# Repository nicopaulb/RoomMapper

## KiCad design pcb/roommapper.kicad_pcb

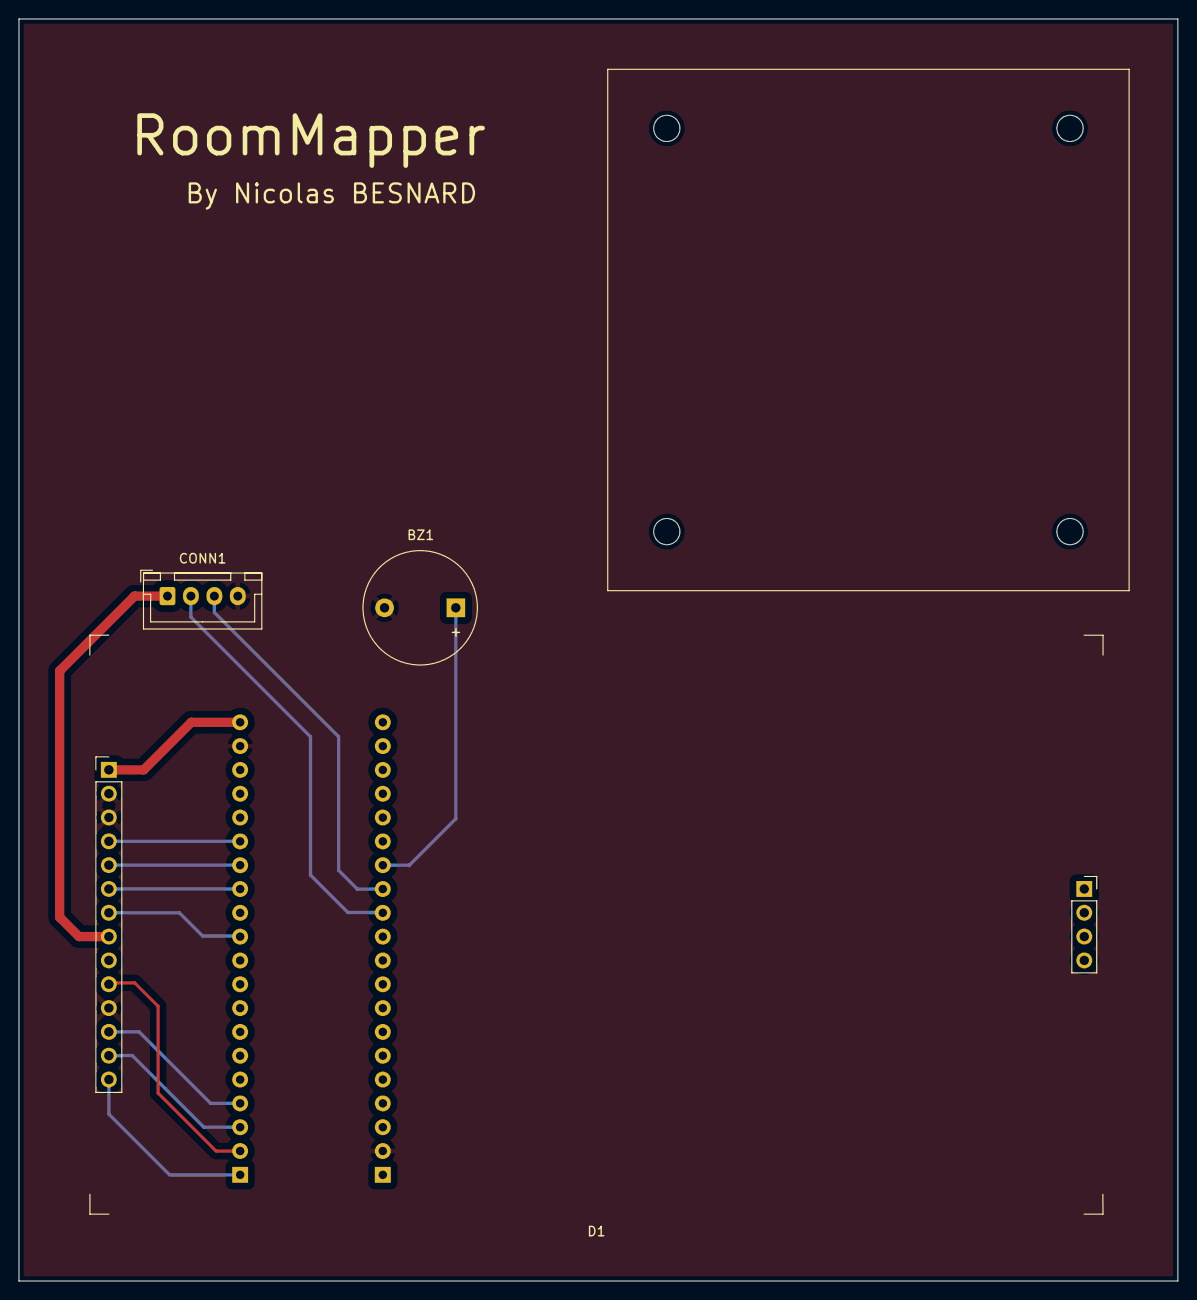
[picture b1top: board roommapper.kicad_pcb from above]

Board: 2 copper layers, 123.6 x 134.6 mm, 4 parts (1 on the bottom side), 14 nets.

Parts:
BZ1: Buzzer; Buzzer_12x9.5RM7.6
CONN1: RPLIDAR_C1; JST_XH_B4B-XH-A_1x04_P2.50mm_Vertical
D1: TFT_480x320; TFT_ILI9488_480x320
U2: STM32F411CEUx_BlackPill; STM32F4x1CxU6 WeActStudio

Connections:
3.3V: D1.1 (VCC), U2.20 (3.3V)
5V: CONN1.1 (VCC), D1.8 (LED), U2.18 (5V)
BUZZER: BZ1.1 (+), U2.27 (TIM2_CH2)
GND: BZ1.2 (-), CONN1.4 (GND), D1.2 (GND), D1.3 (CS), D1.11 (T_CS), U2.19 (GND)
ILI94488_CLK: D1.7 (SCK), U2.11 (SPI1_SCK)
ILI94488_DC: D1.5 (DC), U2.14 (PB6)
ILI94488_MOSI: D1.6 (SDI), U2.13 (SPI1_MOSI)
ILI94488_RST: D1.4 (RST), U2.15 (PB7)
RPLIDAR_RX: CONN1.2 (TX), U2.29 (USART2_RX)
RPLIDAR_TX: CONN1.3 (RX), U2.28 (USART2_TX)
XPT2046_CLK: D1.10 (T_CLK), U2.2 (SPI2_SCK)
XPT2046_INT: D1.14 (T_IRQ), U2.1 (PB12)
XPT2046_MISO: D1.13 (T_DO), U2.3 (SPI2_MISO)
XPT2046_MOSI: D1.12 (T_DIN), U2.4 (SPI2_MOSI)

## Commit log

2025-11-17 Init
2025-11-18 rplidar: implement parser for received messages from RPLidar devices
2025-11-18 test: implement template
2025-11-18 rplidar: fix label can only be part of a statement error
2025-11-18 test: fix test main signature
2025-11-19 rplidar: fix various bug
2025-11-19 test: add new unit tests
2025-11-20 rplidar: implement scan express request
2025-11-20 test: add test for scan express
2025-11-20 test: add new unit test
2025-11-20 rplidar: do not expect more multiple response when a new request is sent
2025-11-21 cubemx: configure project to match STM32 black pill dev board
2025-11-21 cubemx: update ioc file
2025-11-21 project: migrate to STM32CubeIDE 2.0.0
2025-11-26 global: update
2025-11-26 rplidar: add reset function
2025-11-27 rplidar: add blocking options for all requests
2025-11-27 test: fix unit test
2025-11-27 rplidar: add blocking mode for scan requests
2025-11-27 doc: add doxygen documentation for rplidar
2025-11-28 global: save workspace
2025-12-05 display: fix interrupt being triggered while communication is ongoing
2025-12-05 rplidar: fix unsync happening when multiple requests were sent at the same time
2025-12-05 map: add several new features
2025-12-05 rplidar: reduce reset delay from 1000ms to 600ms
2025-12-05 format
2025-12-05 project: update files
2025-12-07 test: fix unit tests
2025-12-08 rplidar: check health status at init
2025-12-08 format: implement formatting rules for code
2025-12-08 rplidar: update doc
2025-12-08 display: rename static functions
2025-12-08 menu: implement menu management and diag screen
2025-12-09 pcb: update
2025-12-10 diag: add exit button
2025-12-10 rplidar: add doc about measurement scaling factor
2025-12-10 buzzer: implement buzzer sound
2025-12-11 general: update project io pins for easier pcb routing
2025-12-11 pcb: remove lock files
2025-12-12 buzzer: add sound effect and volume bar
